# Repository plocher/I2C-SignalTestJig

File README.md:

# I2C-SignalTestJig
## License: CERN Open Hardware Licence v1.2

Test Jig for simple signal panels

An I2C slave board that drives 6x signal head drivers (effectively 3x IOB-Signal circuits)
in a form factor that mimics the panelization spacing of the simple signal boards.

This allows bulk testing after fabrication of an entire board in 2 (or 4) operations 
  * align a board with the pogo pins
  * press down on pins
  * observe the correct operation of the heads
     * mark any defective units
  * move panel to next set of contacts & repeat

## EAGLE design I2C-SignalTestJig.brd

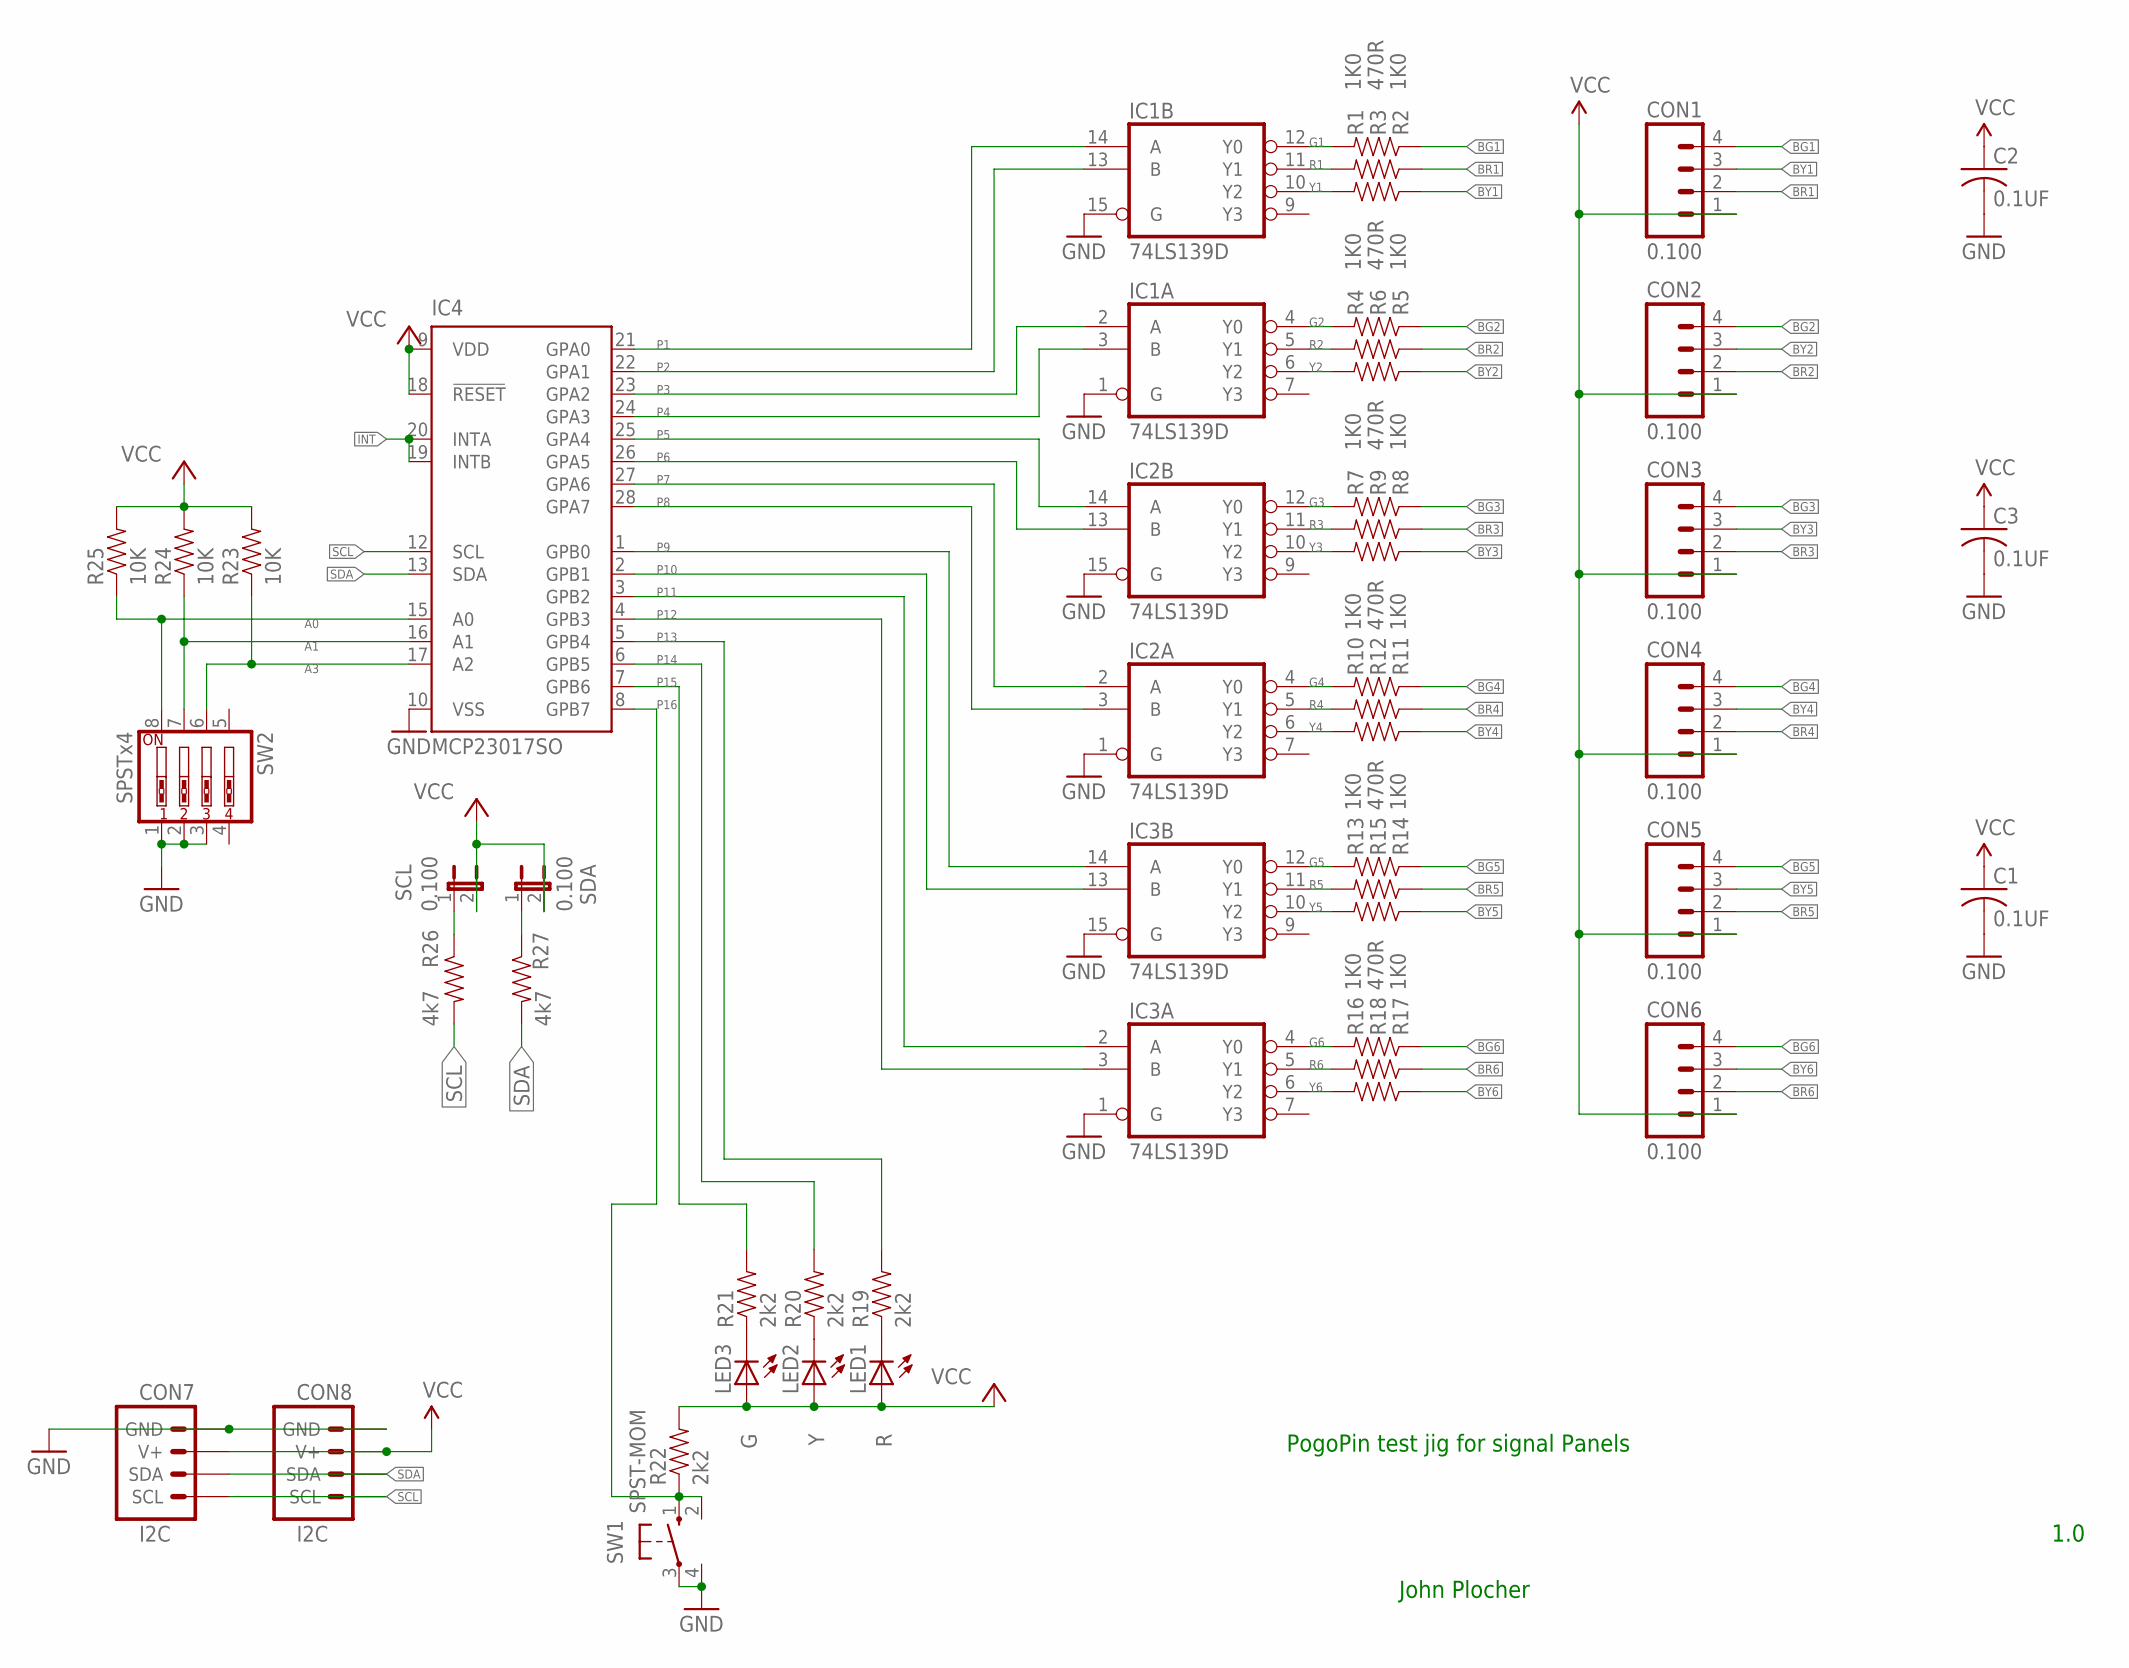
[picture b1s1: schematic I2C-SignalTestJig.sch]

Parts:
C1, C2, C3: 0.1UF; 0603-CAP
CON1, CON2, CON3, CON4, CON5, CON6: 0.100; 1X04_LOCK
CON7, CON8: I2C; I2C-L
IC1, IC2, IC3: 74LS139D; SO16
IC4: MCP23017SO; SO28W
LED1: R; 0603-LED
LED2: Y; 0603-LED
LED3: G; 0603-LED
R1, R2, R4, R5, R7, R8, R10, R11, R13, R14, R16, R17: 1K0; 0805-RES
R3, R6, R9, R12, R15, R18: 470R; 0805-RES
R19, R20, R21, R22: 2k2; 0603-RES
R23, R24, R25: 10K; 0603-RES
R26, R27: 4k7; 0603-RES
SCL: 0.100; 1X02_LOCK
SDA: 0.100; 1X02_LOCK
SW1: SPST-MOM; 4P-PTH-6.0X6.0X5.0H
SW2: SPSTx4; EDG-04

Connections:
!INT: IC4.19 (INTB), IC4.20 (INTA)
A0: IC4.15 (A0), R25.1, SW2.8
A1: IC4.16 (A1), R24.1, SW2.7
A3: IC4.17 (A2), R23.1, SW2.6
BG1: CON1.4, R1.1
BG2: CON2.4, R4.1
BG3: CON3.4, R7.1
BG4: CON4.4, R10.1
BG5: CON5.4, R13.1
BG6: CON6.4, R16.1
BR1: CON1.2, R3.1
BR2: CON2.2, R6.1
BR3: CON3.2, R9.1
BR4: CON4.2, R12.1
BR5: CON5.2, R15.1
BR6: CON6.2, R18.1
BY1: CON1.3, R2.1
BY2: CON2.3, R5.1
BY3: CON3.3, R8.1
BY4: CON4.3, R11.1
BY5: CON5.3, R14.1
BY6: CON6.3, R17.1
G1: IC1.12 (Y0), R1.2
G2: IC1.4 (Y0), R4.2
G3: IC2.12 (Y0), R7.2
G4: IC2.4 (Y0), R10.2
G5: IC3.12 (Y0), R13.2
G6: IC3.4 (Y0), R16.2
GND: C1.2, C2.2, C3.2, CON7.GND, CON7.GND@1 (GND), CON8.GND, CON8.GND@1 (GND), IC1.1 (G), IC1.8 (GND), IC1.15 (G), IC2.1 (G), IC2.8 (GND), IC2.15 (G), IC3.1 (G), IC3.8 (GND), IC3.15 (G), IC4.10 (VSS), SW1.3, SW1.4 (P1), SW2.1, SW2.2, SW2.3
unnamed: LED3.C, R21.1
unnamed: LED2.C, R20.1
unnamed: LED1.C, R19.1
unnamed: R26.1, SCL.1
unnamed: R27.1, SDA.1
P1: IC1.14 (A), IC4.21 (GPA0)
P2: IC1.13 (B), IC4.22 (GPA1)
P3: IC1.2 (A), IC4.23 (GPA2)
P4: IC1.3 (B), IC4.24 (GPA3)
P5: IC2.14 (A), IC4.25 (GPA4)
P6: IC2.13 (B), IC4.26 (GPA5)
P7: IC2.2 (A), IC4.27 (GPA6)
P8: IC2.3 (B), IC4.28 (GPA7)
P9: IC3.14 (A), IC4.1 (GPB0)
P10: IC3.13 (B), IC4.2 (GPB1)
P11: IC3.2 (A), IC4.3 (GPB2)
P12: IC3.3 (B), IC4.4 (GPB3)
P13: IC4.5 (GPB4), R19.2
P14: IC4.6 (GPB5), R20.2
P15: IC4.7 (GPB6), R21.2
P16: IC4.8 (GPB7), R22.1, SW1.1 (S), SW1.2 (S1)
R1: IC1.11 (Y1), R3.2
R2: IC1.5 (Y1), R6.2
R3: IC2.11 (Y1), R9.2
R4: IC2.5 (Y1), R12.2
R5: IC3.11 (Y1), R15.2
R6: IC3.5 (Y1), R18.2
SCL: CON7.SCL, CON7.SCL@1 (SCL), CON8.SCL, CON8.SCL@1 (SCL), IC4.12 (SCL), R26.2
SDA: CON7.SDA, CON7.SDA@1 (SDA), CON8.SDA, CON8.SDA@1 (SDA), IC4.13 (SDA), R27.2
VCC: C1.1, C2.1, C3.1, CON1.1, CON2.1, CON3.1, CON4.1, CON5.1, CON6.1, CON7.V+, CON7.V+@1 (V+), CON8.V+, CON8.V+@1 (V+), IC1.16 (VCC), IC2.16 (VCC), IC3.16 (VCC), IC4.9 (VDD), IC4.18 (!RESET), LED1.A, LED2.A, LED3.A, R22.2, R23.2, R24.2, R25.2, SCL.2, SDA.2
Y1: IC1.10 (Y2), R2.2
Y2: IC1.6 (Y2), R5.2
Y3: IC2.10 (Y2), R8.2
Y4: IC2.6 (Y2), R11.2
Y5: IC3.10 (Y2), R14.2
Y6: IC3.6 (Y2), R17.2

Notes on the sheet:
PogoPin test jig for signal Panels
John Plocher
1.0

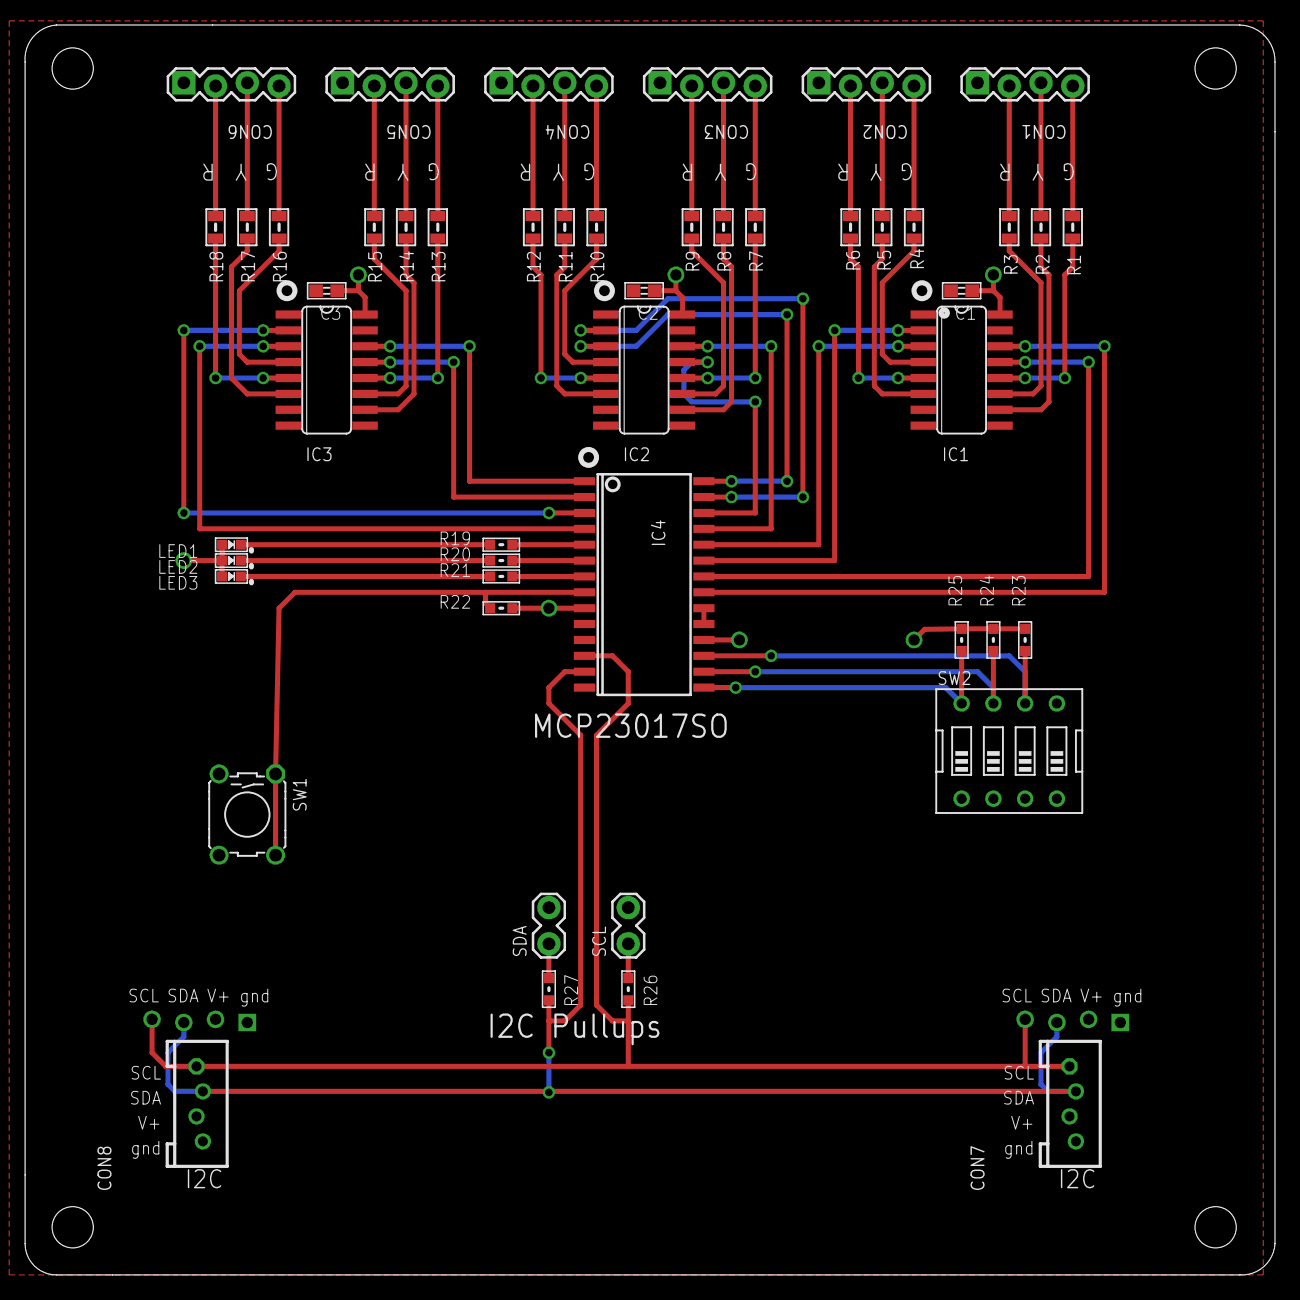
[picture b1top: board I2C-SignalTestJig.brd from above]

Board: 2 copper layers, 100.0 x 100.0 mm, 50 parts (0 on the bottom side), 65 nets.

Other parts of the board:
BOARD1: BOARD; BOARD-SEEED10X10-NOHOLES

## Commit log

2020-04-30 Initial version
2020-05-04 updated tags
2020-10-05 added values for connectors
2020-10-06 normalized values
